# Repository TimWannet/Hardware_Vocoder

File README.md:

# Hardware_Vocoder

## Table of Contents
- [Introduction](#introduction)
- [Features](#features)
- [Installation](#installation)
- [Usage](#usage)
- [Contributing](#contributing)
- [License](#license)

## Introduction
Coming soon

## Features
Coming soon

## Installation
1. Clone the repository:
    ```bash
    git clone https://github.com/yourusername/Hardware_Vocoder.git
    ```
2. Navigate to the project directory:
    ```bash
    cd Hardware_Vocoder
    ```

3. Install [PlatformIO IDE](https://platformio.org/install/ide?install=vscode) for Visual Studio Code.

4. (Linux only) Install UDEV Rules

5. Open the project in Visual Studio Code.

6. Configure the `platformio.ini` file in the project directory with the following content:
    ```ini
    [env:teensy40]
    platform = teensy
    board = teensy41
    framework = arduino
    ```
7. Connect your Teensy board to your computer.

8. Build and upload the project to the Teensy board:
    ```bash
    pio run --target upload
    ```
9. Verify the installation by checking the serial monitor for output from the Teensy board.

## Usage
Coming soon 

## Contributing
Coming soon

## License
The licence for this project is still being

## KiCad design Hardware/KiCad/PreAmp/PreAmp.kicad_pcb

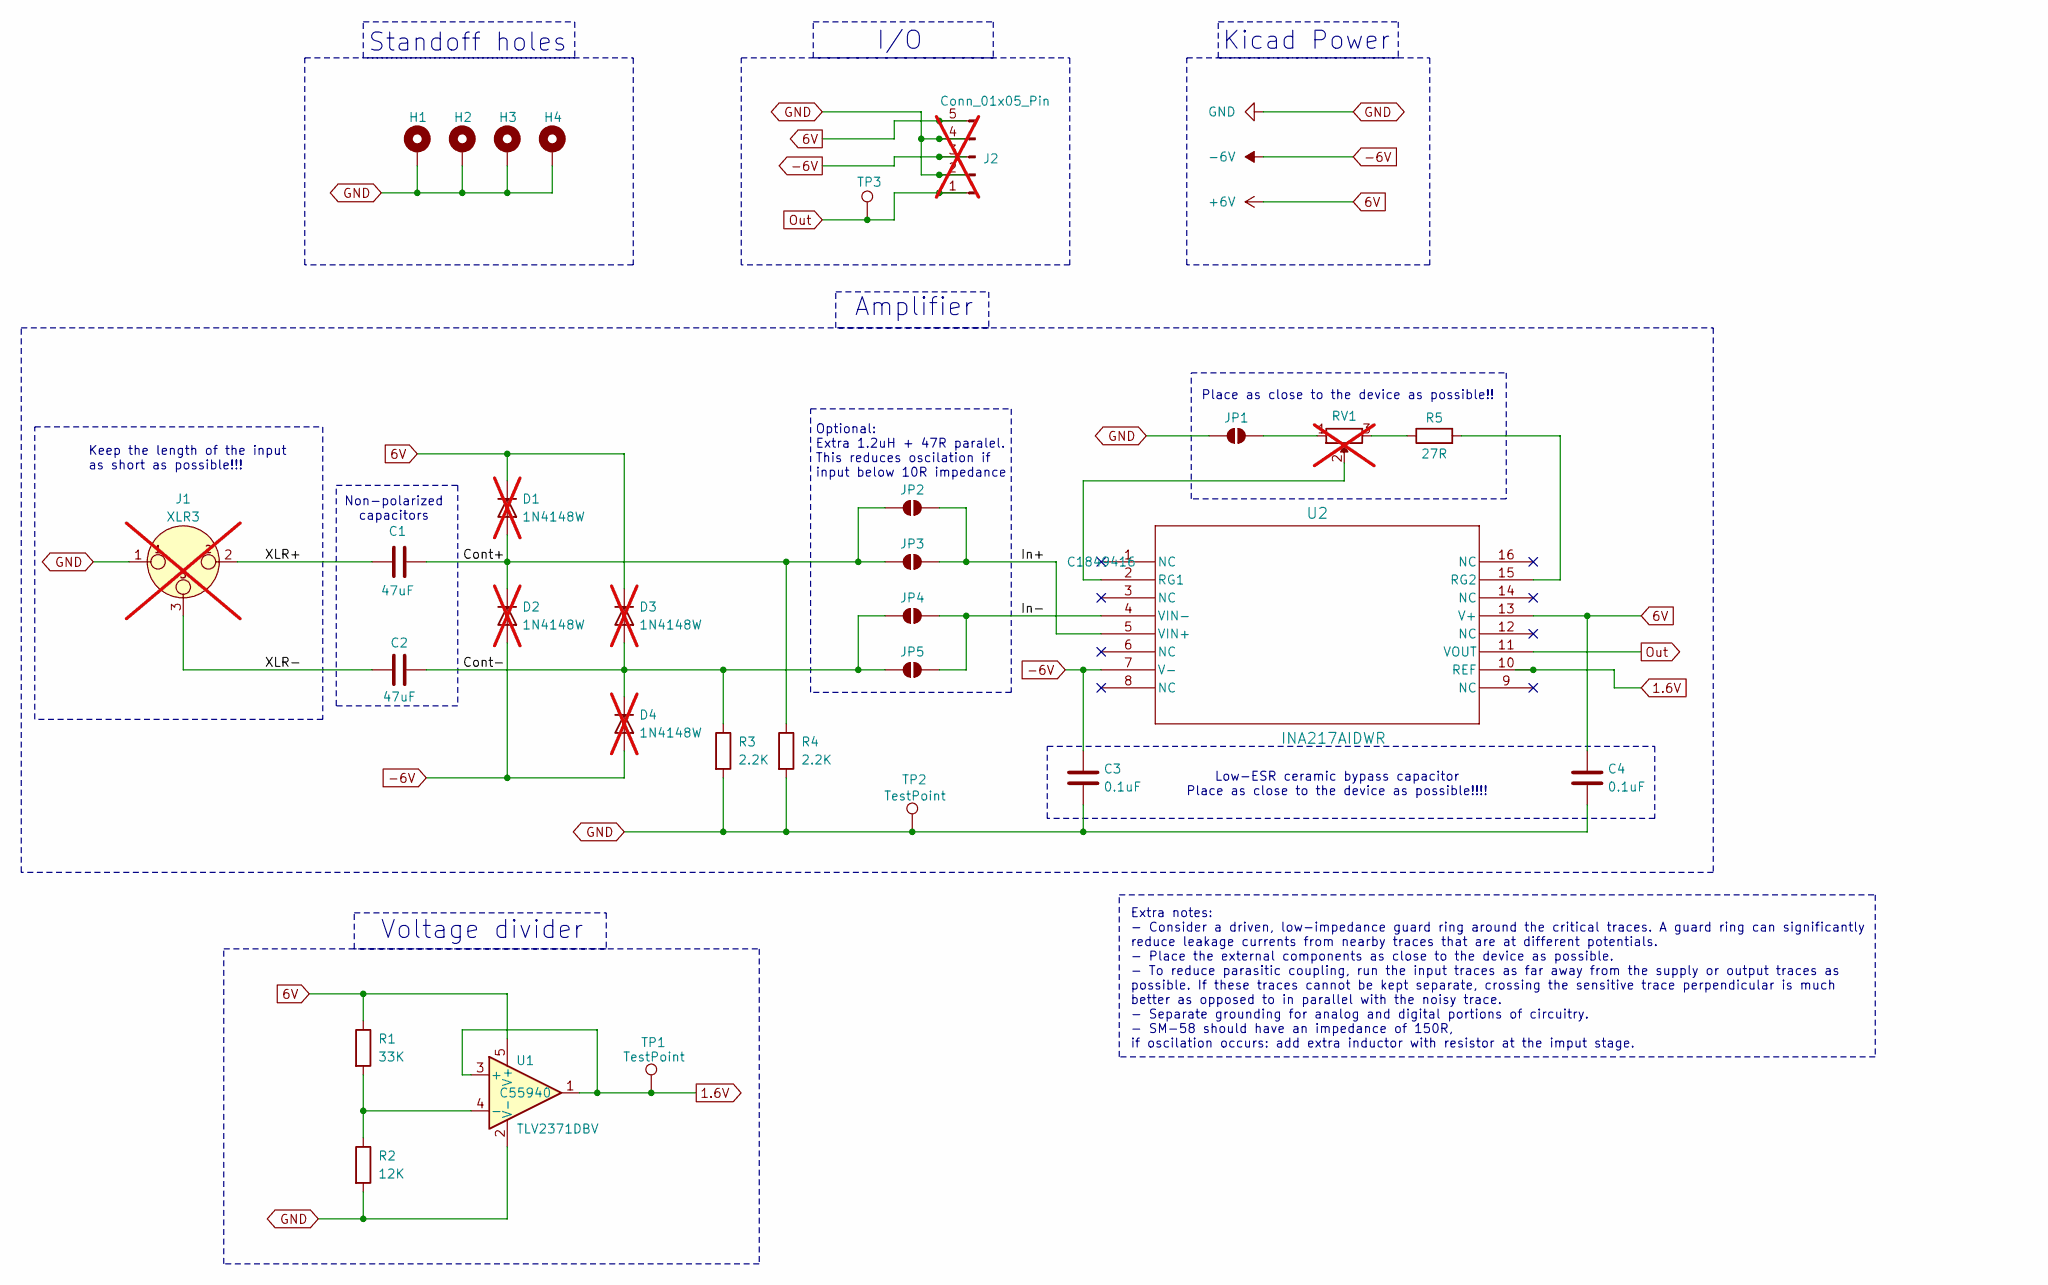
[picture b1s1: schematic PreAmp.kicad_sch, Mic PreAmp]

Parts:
C1, C2: 47uF; C_1206_3216Metric; LCSC PN C76659
C3, C4: 0.1uF; CP_EIA-3216-18_Kemet-A; LCSC PN C7173
D1, D2, D3, D4: 1N4148W; D_DO-35_SOD27_P7.62mm_Horizontal; not fitted
H1, H2, H3, H4: MountingHole_Pad; MountingHole_3.2mm_M3_DIN965_Pad_TopBottom
J1: XLR3; Jack_XLR_Neutrik_NC3FAAV-0_Vertical; not fitted
J2: Conn_01x05_Pin; PinHeader_1x05_P2.54mm_Vertical; not fitted
JP1, JP2, JP3, JP4, JP5: SolderJumper_2_Open; SolderJumper-2_P1.3mm_Open_Pad1.0x1.5mm
R1: 33K; C_0805_2012Metric; LCSC PN C17633
R2: 12K; C_0805_2012Metric; LCSC PN C2907225
R3, R4: 2.2K; C_0805_2012Metric; LCSC PN C17594
R5: 27R; C_0805_2012Metric; LCSC PN C17594
RV1: R_Potentiometer; Potentiometer_Alpha_RD901F-40-00D_Single_Vertical; not fitted
TP1, TP2, TP3: TestPoint; TestPoint_Pad_D2.0mm
U1: TLV2371DBV; SOT-23-5; LCSC PN C55940
U2: INA217AIDWR; DW16; LCSC PN C1849416

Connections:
1.6V: TP1.1, U1.1, U1.3 (+), U2.10 (REF)
6V: C4.1, D1.1 (K), D3.1 (K), J2.5, R1.1, U1.5 (V+), U2.13 (V+)
-6V: C3.1, D2.2 (A), D4.2 (A), J2.3, U2.7 (V-)
/Cont+: C1.2, D1.2 (A), D2.1 (K), JP2.2 (B), JP3.2 (B), R4.1
/Cont-: C2.2, D3.2 (A), D4.1 (K), JP4.2 (B), JP5.2 (B), R3.1
/In+: JP2.1 (A), JP3.1 (A), U2.5 (VIN+)
/In-: JP4.1 (A), JP5.1 (A), U2.4 (VIN-)
/XLR+: C1.1, J1.2
/XLR-: C2.1, J1.3
GND: C3.2, C4.2, H1.1, H2.1, H3.1, H4.1, J1.1, J2.2, J2.4, JP1.2 (B), R2.2, R3.2, R4.2, TP2.1, U1.2 (V-)
unnamed: JP1.1 (A), RV1.1
unnamed: R5.1, RV1.3
unnamed: R1.2, R2.1, U1.4 (-)
unnamed: RV1.2, U2.2 (RG1)
unnamed: R5.2, U2.15 (RG2)
Out: J2.1, TP3.1, U2.11 (VOUT)

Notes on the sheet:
Optional: Extra 1.2uH + 47R paralel. This reduces oscilation if input below 10R impedance
Standoff holes
Extra notes: - Consider a driven, low-impedance guard ring around the critical traces. A guard ring can significantly reduce leakage currents from nearby traces that are at different potentials. - Place the external components as close to the device as possible. - To reduce parasitic coupling, run 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
Low-ESR ceramic bypass capacitor Place as close to the device as possible!!!!
Voltage divider
Place as close to the device as possible!!
Amplifier
Kicad Power
Non-polarized capacitors
Keep the length of the input as short as possible!!!
I/O

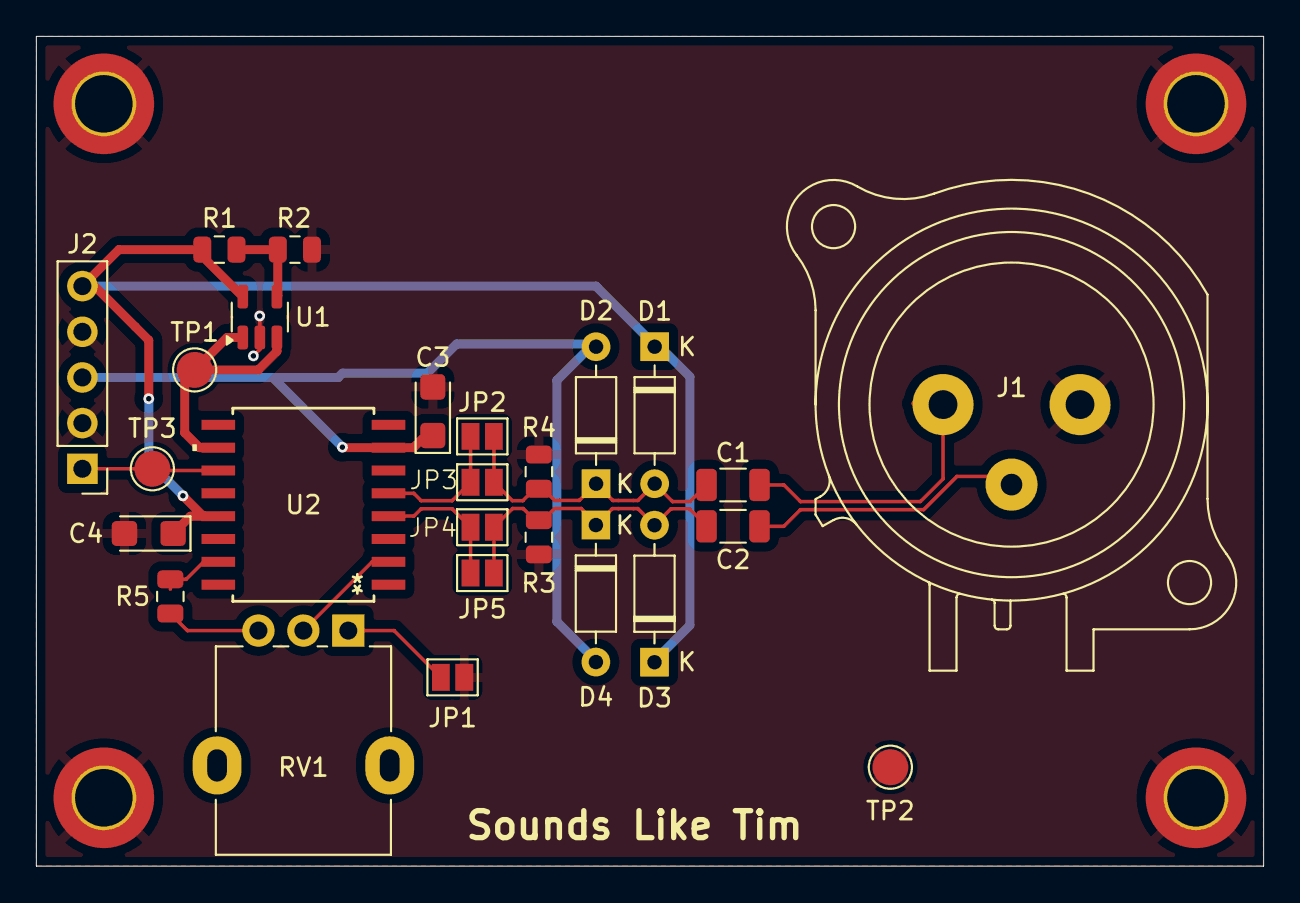
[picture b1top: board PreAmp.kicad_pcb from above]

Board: 2 copper layers, 68.3 x 46.2 mm, 30 parts (0 on the bottom side), 16 nets.

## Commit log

2025-03-04 update gitignore with .vscode directory
2025-03-04 update readme with init template
2025-03-04 init build software
2025-03-04 test blink
2025-03-06 implements new features: modulator sampling, arm_fft, gaining magnatude and phase function
2025-03-10 Fix fft bug, fix input logic & implement sgtl5000_1 Audio shield
2025-03-11 add bool for testing with serial comm
2025-03-12 Inverse FFT for Carrier working (only for 128 samples), organised code
2025-03-24 Complete re-design of the code, now with Interrupts to handle sampling and transfer. /bugfix for the FFT_SIZE
2025-03-24 Get Magnitude and phace function
2025-03-24 Doxygen comments for function
2025-03-24 feature: int to float function
2025-03-26 Switch case function for different fft sizes with arm_cfft_sR_f32_len128
2025-03-26 doxygen introduction
2025-03-26 Split fft and inverse fft
2025-03-26 updated doxygen comments with parameters
2025-03-27 float to int function
2025-03-27 modulator buffer check in loop
2025-03-27 better renaming of processors
2025-03-27 new function prototype
2025-03-27 correction for renaming variables
2025-03-27 Update Doxygen comments
2025-03-31 Bugfix -> reset index to get proper values
2025-04-03 Vocoder function works with smoothing of modulator (tested!)
2025-04-03 created Hardware file
2025-04-03 Created titles
2025-04-03 Imported OPA1656 into project and library
2025-04-03 Created Spice simulation, starting with opamp template
2025-04-09 OPA1656 Imported
2025-04-09 Implemented High Pass filter function
2025-04-09 Schematic with 2 opamps, XLR to onewire (Need: tested & grounded)
2025-04-09 Re-organised schematic and simulation in own directory
2025-04-15 V1 Microphone circuit (simulated in LTSpice)
2025-04-15 removed
2025-04-15 created 5V USB-C Power supply (simple version for now)
2025-04-15 Hierarchical sheet for MCU
2025-04-16 Midi in circuit with optocoupler and isolation/input protection
2025-04-16 Labeled, sheet out from modulator
2025-04-22 2nd simulation based on 3 Opa1656
2025-04-22 simulation 1 based on 2 Opa1656
2025-04-22 Re-orginanisation
2025-05-06 created new simulation with Ina217
2025-05-06 First trial without DC loop
2025-05-06 V1 for the schematic (Looks promising)
2025-05-07 Excanged Opamp for TVL2371
2025-05-07 Created seperate KiCad for PreAmp
2025-05-07 Header pins for input and output
2025-05-07 Inserted XLR plug
2025-05-07 created XLR input
2025-05-07 Voltage divider circuit
2025-05-07 Circuit before V_In
2025-05-07 Connected REF and Output
2025-05-07 Only local folder
2025-05-07 Reorganised+rename Main_Board project
2025-05-07 Relocated PreAmp project
2025-05-07 Not needed
2025-05-07 Potmeter for amplification
2025-05-07 Datasheet comments + extra test points added
2025-05-08 Imported PCB components
2025-05-08 Changed flow -> right to left
2025-05-08 Layout everything globaly
2025-05-08 Changed Header pin
2025-05-08 First layout
2025-05-08 Equal length traces for Hot and Cold
2025-05-08 First part of differential routing
2025-05-08 Removed 4 jumper points
2025-05-08 Connected everything together
2025-05-08 Lower ground plane
2025-05-08 V1 done
2025-05-08 Added version number and date
2025-05-09 Put back the 4 jumpers for possible improvement (reduce oscilation)
2025-05-09 Improved trough feedback Tijmen
2025-05-09 Included text on PCB
2025-05-12 Generated files for production
2025-05-12 Corrected collums
2025-05-15 Send to production
2025-05-20 Created utils
2025-05-20 Created audio_stream_classes
2025-05-20 Removed functions
2025-05-20 changed
2025-05-20 Changed date
2025-05-20 First init of screen_base.h
2025-05-20 first init of Main_Menu.h/cpp
2025-05-20 init for Manager
2025-05-21 added ifndef
2025-05-21 Comments
2025-05-21 Included TFT screen into main
2025-05-26 Relocate includes
2025-05-26 dynamic modular menu
2025-05-26 update input event
2025-05-26 created input manager for encoder input
2025-05-26 created redraw
2025-05-26 modular main menu with input event
2025-05-26 added encoder
2025-05-26 imported TPS65133 for PSU
2025-05-26 New footprint based on datasheet
2025-05-27 V1 PSU with double rail
2025-05-27 Added headers and mounting holes for connection with other PCB
2025-05-27 Backups
2025-05-27 Added PSU hierarchical inputs and outputs
2025-05-27 Created Female header connections for MCU
2025-05-27 Experimental test points for USB data
2025-05-28 Mirrored pinout
2025-05-28 added headers for teensy
2025-05-28 Header for fft Screen
2025-05-28 Interface hierarchical out for screen and encoder
2025-05-28 mirrored pinout so 1 is up top
2025-05-28 Screen pinout for MCU
2025-05-28 Connected screen, USB and encoder in the main sheet
2025-05-28 Inserted SGTL5000 for the IO
2025-05-28 Changed outlining and combined input and main out
2025-06-11 Update before switching over
2025-06-24 Changed screen type (Tested)
2025-06-24 Removed debug comment
2025-06-24 Noise function with voice and unvoice options
2025-06-26 Implement main menu navigation to settings
2025-06-26 Navigation back to main menu
2025-06-26 Noise parameters, now with select and confirm option
2025-06-26 overclock
